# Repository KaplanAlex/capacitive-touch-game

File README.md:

# capacitive-touch-game
ELEC 327 Final Project

Alexander Kaplan,
Alfonso Morera,
Neil Seoni

**Video Demo**

**Overview**

Our project focused on the design and implementation of capacitive touch buttons as well as management of large quantities of data (relative to the MSP430G3553’s 512 bytes). We designed a PCB with five capacitive touch buttons which interacted with an 8x16 LED grid via SPI to play interactive arcade games. In addition to the hardware, we developed a capacitive touch library to detect presses from our capacitive touch buttons. We designed this library to be easily calibrated for capacitive touch pads with different sensitivities. 

Our design emphasized all of major concepts of microcontroller programming we covered in this course including: low power modes, timers, PWM, and interaction with hardware modules (SPI communication).

**Design**

As briefly mentioned in the Overview section, we created a capacitive touch based game through the development of the following distinct components: a PCB with five capacitive touch buttons, an 8x16 WS2812 LED grid, a capacitive touch library, a memory reduced SPI driven WS2812 communication library, and the stacker arcade game logic. The design of each of these discrete aspects of the project is outlined below:

**PCB**

As depicted in the image below, our PCB interface consisted of five circular 0.5” pads which served as up, down, left, right, and center capacitive touch buttons, as well as a five LED display (bottom left) representing the buttons’ pressed states. 

**Figure 1: PCB Board Design**

Each pad was connected in parallel with a PWM signal’s path from P2.1 to one of five receive pins (P2.2-P2.6) as shown in the figure below.

**Figure 2: PWM Signal Path**

This structure setup each pad to act as half of a capacitor, with our bodies modeled as the other half of the capacitor connected to ground. Thus, touching a pad completed the capacitor and delayed the transmission of the PWM pulse. Our capacitive touch library used the transmission time delay from touching a pad to detect presses (the specifics of the library implementation are discussed in a later section).

To increase the sensitivity and reliability of these capacitive touch pads, our PCB design was centered around the isolation of the pads from all other circuit elements. We minimized capacitive noise by putting only the pads and their corresponding leds on the top of the PCB. Additionally, we covered all open space on the top of the PCB with a ground plate, which neutralized potential capacitive interference from the PCB material.

It is also important to note that to compensate for the large power consumption of our LED grid (discussed in the following section) while ensuring the MSP430 isn’t overpowered, the PCB board routes power from two sources: a 3V coin battery which powers the MSP430 and 5V DC power from a wall outlet which powers the NeoPixel LED grid. We choose to route these sources through the PCB to facilitate the connection of both power supplies to the same ground. By connecting the two grounds, we mitigated any potential issues transmitting SPI signals from the MSP430 to the LED grid.

**WS2812 LED Boards**

**Figure 3: LED Grid**

We created an 8x16 led grid from two 8x8 NeoPixel blinky boards. These LEDs use an NRZ protocol to determine their color and forward information through the chain. This protocol does not rely on a clock signal, as it requires only a single wire for data transmission. Consequently, bits cannot be sent simply as pulses with high representing 1 and off representing 0, as the LEDs have no timing coordination with transmission. Instead, the W2812 NRZ protocol requires each transmitted bit to be encoded as a long (550 - 850ns) or short (200 - 500ns) pulse representing a 1 or a 0 respectively.

Ultimately, we capitalized on the timing and transmission capabilities of the MSP430 SPI module to communicate via these NRZ specifications. We masked out each bit we transmitted, then sent a 750ns pulse to represent ones and a 375ns pulse to represent zeros. We created these pulse times by calibrating the MSP430 clock to 16MHz and setting the SPI module bit transmission time to 187.5ns. Then, we used the SPI module to transmit 0b11110000 as a long pulse and 0b11000000 as a short pulse, as each bit is written as high or low for 187.5ns. 

The WS2812 leds required 3 bytes corresponding to 8 bit color in GRB format. To compensate for the small program memory of the MSP430, we designed internal state which encoded the color of each LED in a single byte and functions to expand encoded colors to their corresponding 3 byte GRB representation prior to transmission. 

**Capacitive Touch Library**

To detect capacitive touch, we constructed a library which tracks the transmission time of PWM signals through the pads to five separate receive pins. Touching a capacitive pad increases the pads capacitance and delays the PWM signal transmission. This library utilizes this delay to detect presses by flagging transmission times greater than a specified threshold. We designed this library to be easily calibrated to different pads and sensitivities by abstracting the PWM time parameters and threshold to macros.

**Arcade Games**

To demonstrate the capabilities of our capacitive touch pad, we created two arcade style games accessible from a global start state. At the start pressing either the right or up pad starts the dodge game. In this game, the player uses the pads to move up, down, left, and right on the board to dodge move between blocks which randomly spawn and fall in rows from the top of the screen. This game continues indefinitely until the player collides with a falling block, at which point the lose animation plays and the game returns to the start state. Pressing any other combination of pads starts stacker. In this game, a set number of blocks slides specific to the row back and forth across the screen. Touching any pad stops the row and starts sliding a block above the previous row. Any blocks which don’t align with the previous row are lost, leaving fewer blocks for the next row to be aligned with. Upon reaching the top of the board, the player wins the game and returns to the start, game select state.  All timing for these games was done in 1ms increments, allowing the MSP430 to enter LMP0 during game delays (player/ block movement speed). Additionally, we designed our program such that the capacitive touch sensing was separated from the game logic and thus was not impacted by the 1ms delays.

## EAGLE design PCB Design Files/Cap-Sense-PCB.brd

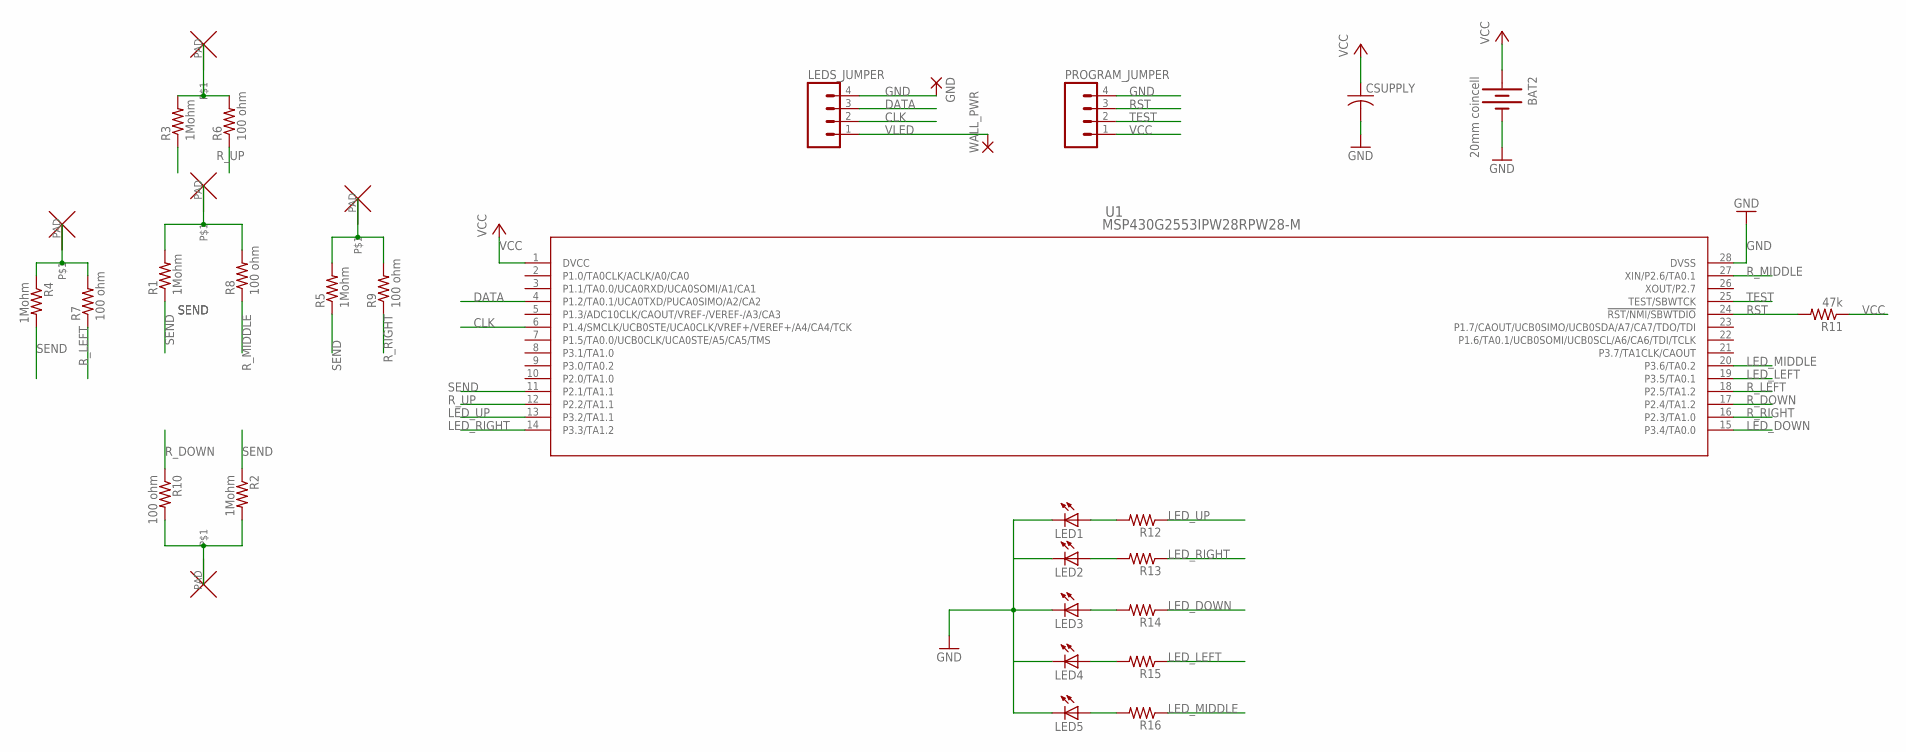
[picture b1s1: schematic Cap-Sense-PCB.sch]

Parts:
BAT2: 20mm coincell; BATTCON_20MM_PTH_COMPACT
CSUPPLY: C-USC1206; C1206
DOWN: KAP_PAD
GND: SMD5; SMD2,54-5,08
LED1, LED2, LED3, LED4, LED5: LEDCHIPLED_1206; CHIPLED_1206
LEDS_JUMPER: M04LOCK; 1X04_LOCK
LEFT: KAP_PAD
MIDDLE: KAP_PAD
PROGRAM_JUMPER: M04LOCK; 1X04_LOCK
R1, R2, R3, R4, R5: 1Mohm; R1206
R6, R7, R8, R9, R10: 100 ohm; R1206
R11: 47k; R1206
R12, R13, R14, R15, R16: R-US_R1206; R1206
RIGHT: KAP_PAD
U1: MSP430G2553IPW28RPW28-M; PW28-M
UP: KAP_PAD
WALL_PWR: SMD5; SMD2,54-5,08

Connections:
CLK: LEDS_JUMPER.2, U1.6 (P1.4/SMCLK/UCB0STE/UCA0CLK/VREF+/VEREF+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)
DATA: LEDS_JUMPER.3, U1.4 (P1.2/TA0.1/UCA0TXD/PUCA0SIMO/A2/CA2)
DOWN: DOWN.PAD, R2.2, R10.2
GND: BAT2.2 (-), CSUPPLY.2, GND.1, LED1.C, LED2.C, LED3.C, LED4.C, LED5.C, LEDS_JUMPER.4, PROGRAM_JUMPER.4, U1.28 (DVSS)
LED_DOWN: R14.1, U1.15 (P3.4/TA0.0)
LED_LEFT: R15.1, U1.19 (P3.5/TA0.1)
LED_MIDDLE: R16.1, U1.20 (P3.6/TA0.2)
LED_RIGHT: R13.1, U1.14 (P3.3/TA1.2)
LED_UP: R12.1, U1.13 (P3.2/TA1.1)
LEFT: LEFT.PAD, R4.1, R7.2
MIDDLE: MIDDLE.PAD, R1.2, R8.2
unnamed: LED1.A, R12.2
unnamed: LED2.A, R13.2
unnamed: LED3.A, R14.2
unnamed: LED4.A, R15.2
unnamed: LED5.A, R16.2
RIGHT: R5.2, R9.2, RIGHT.PAD
RST: PROGRAM_JUMPER.3, R11.2, U1.24 (!RST/NMI/SBWTDIO)
R_DOWN: R10.1, U1.17 (P2.4/TA1.2)
R_LEFT: R7.1, U1.18 (P2.5/TA1.2)
R_MIDDLE: R8.1, U1.27 (XIN/P2.6/TA0.1)
R_RIGHT: R9.1, U1.16 (P2.3/TA1.0)
R_UP: R6.1, U1.12 (P2.2/TA1.1)
SEND: R1.1, R2.1, R3.1, R4.2, R5.1, U1.11 (P2.1/TA1.1)
TEST: PROGRAM_JUMPER.2, U1.25 (TEST/SBWTCK)
UP: R3.2, R6.2, UP.PAD
VCC: BAT2.1 (+), BAT2.3 (+), BAT2.4 (+), BAT2.5 (+), CSUPPLY.1, PROGRAM_JUMPER.1, R11.1, U1.1 (DVCC)
VLED: LEDS_JUMPER.1, WALL_PWR.1

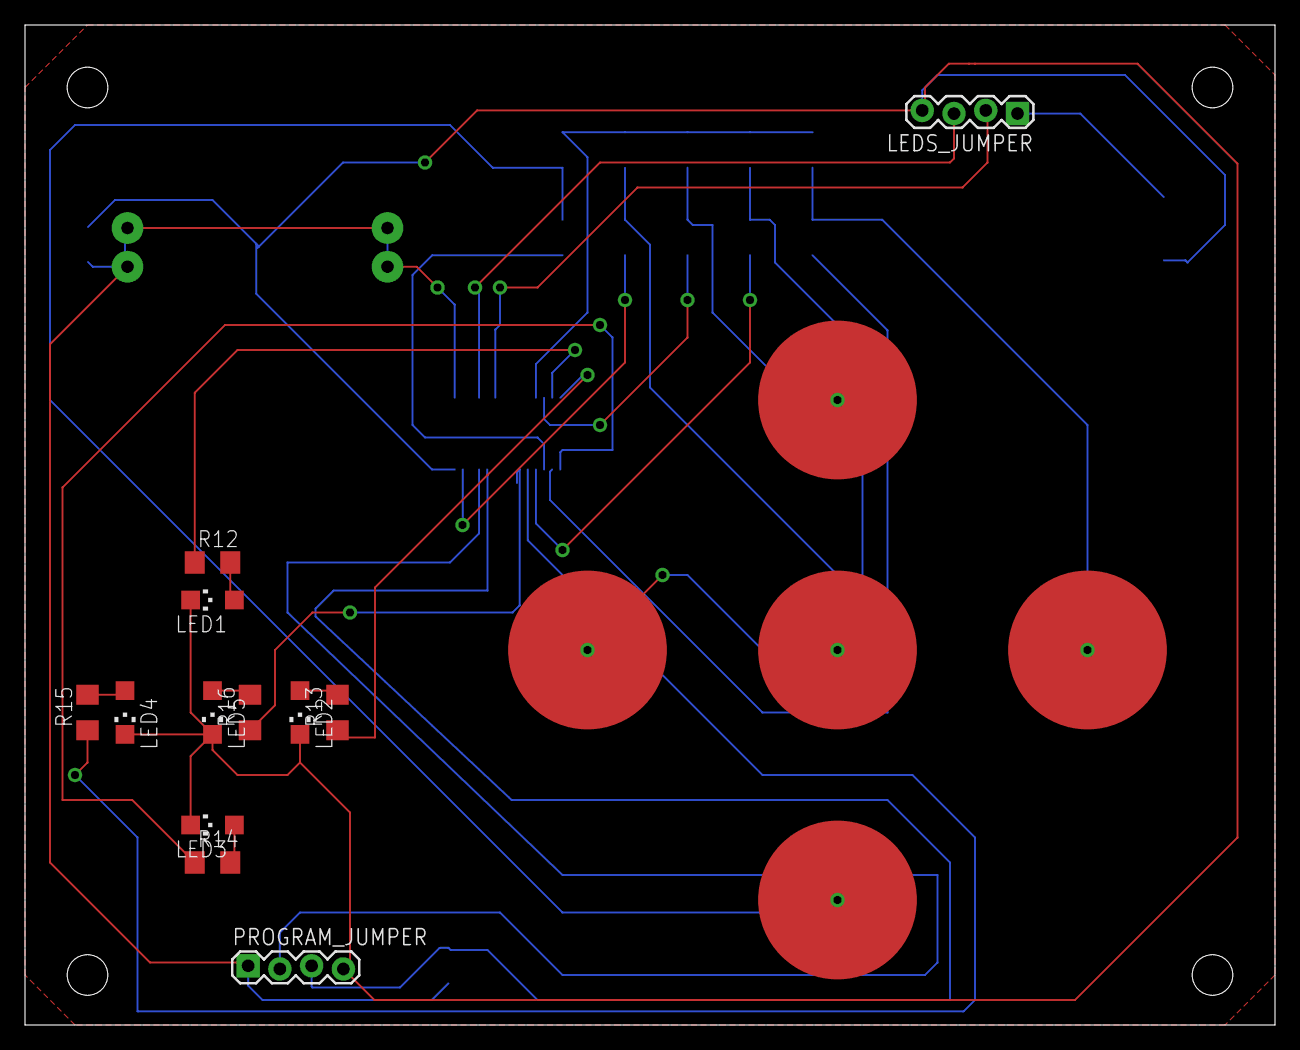
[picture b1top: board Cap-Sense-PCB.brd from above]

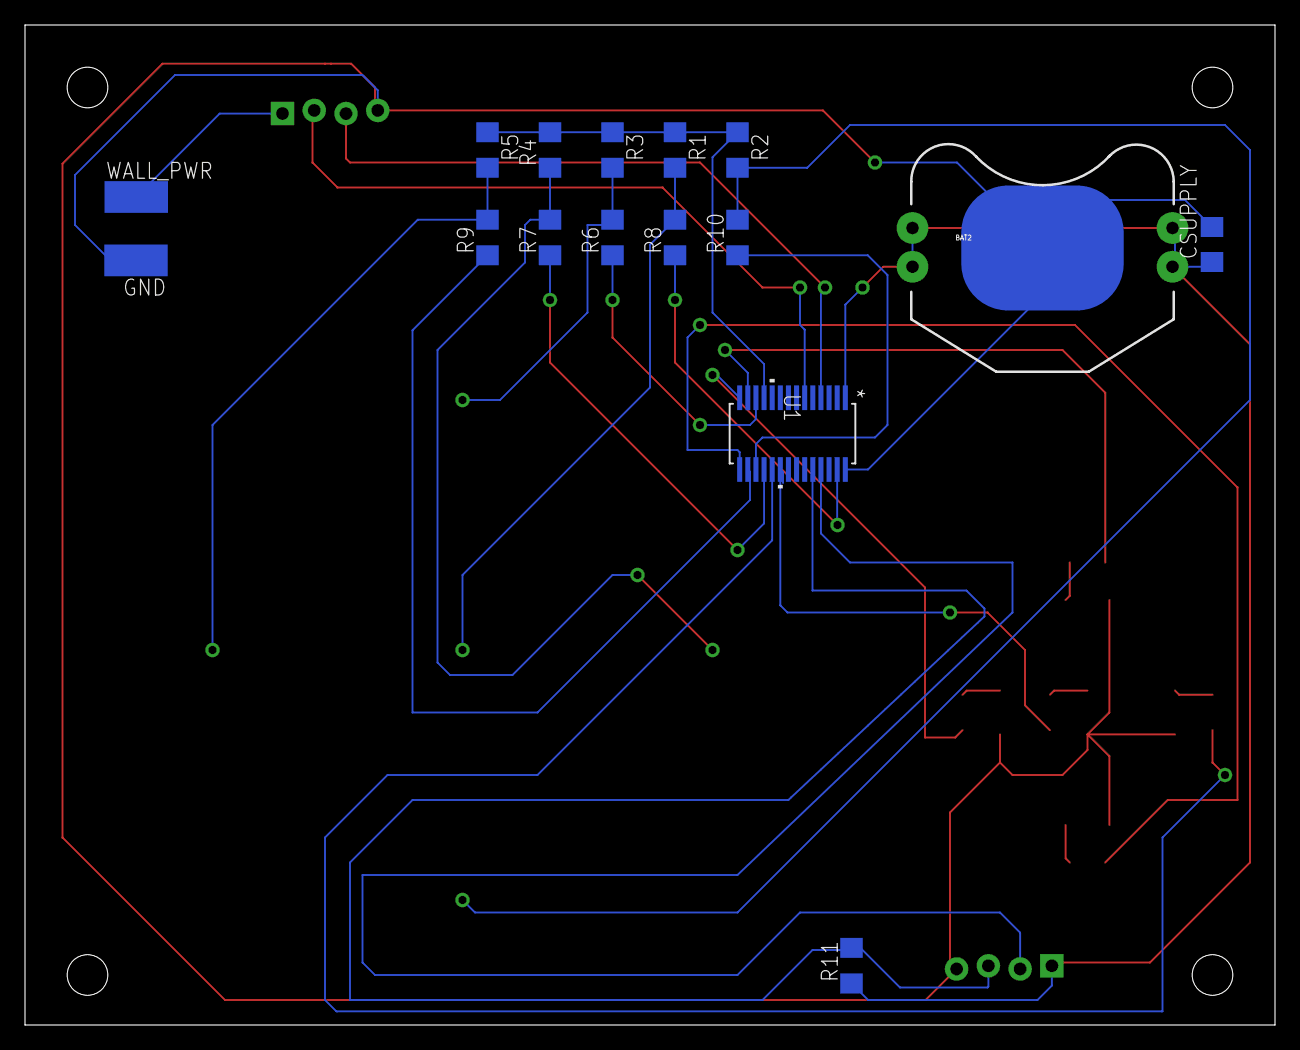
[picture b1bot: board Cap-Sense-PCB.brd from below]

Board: 2 copper layers, 100.0 x 80.0 mm, 33 parts (16 on the bottom side), 28 nets.

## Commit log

2018-04-24 PCB design
2018-04-24 test
2018-04-24 thinking about capacitance
2018-04-25 separate setup file
2018-04-25 potential capacitive sensing
2018-04-25 press led visuals
2018-04-25 cap sense file
2018-04-25 file structure
2018-04-28 reduced spi
2018-04-29 new branch!
2018-04-29 have fun
2018-04-29 They lit up!
2018-04-29 better timing
2018-04-29 starting fsm
2018-04-29 fsm progresss
2018-04-29 should be fading!?
2018-04-29 Stacking!
2018-04-30 works on small board.
2018-04-30 dodge game
2018-04-30 working
2018-05-01 description
2018-05-01 led_control
2018-05-29 video
2018-05-29 video picture
2018-05-29 removed https
2018-05-29 trying again
2018-05-29 screenshot
2018-05-30 images
2018-05-30 formatting

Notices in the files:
parts and their libraries:
SparkFun: Licensing: CC v3.0 Share-Alike You are welcome to use this library for commercial purposes.
